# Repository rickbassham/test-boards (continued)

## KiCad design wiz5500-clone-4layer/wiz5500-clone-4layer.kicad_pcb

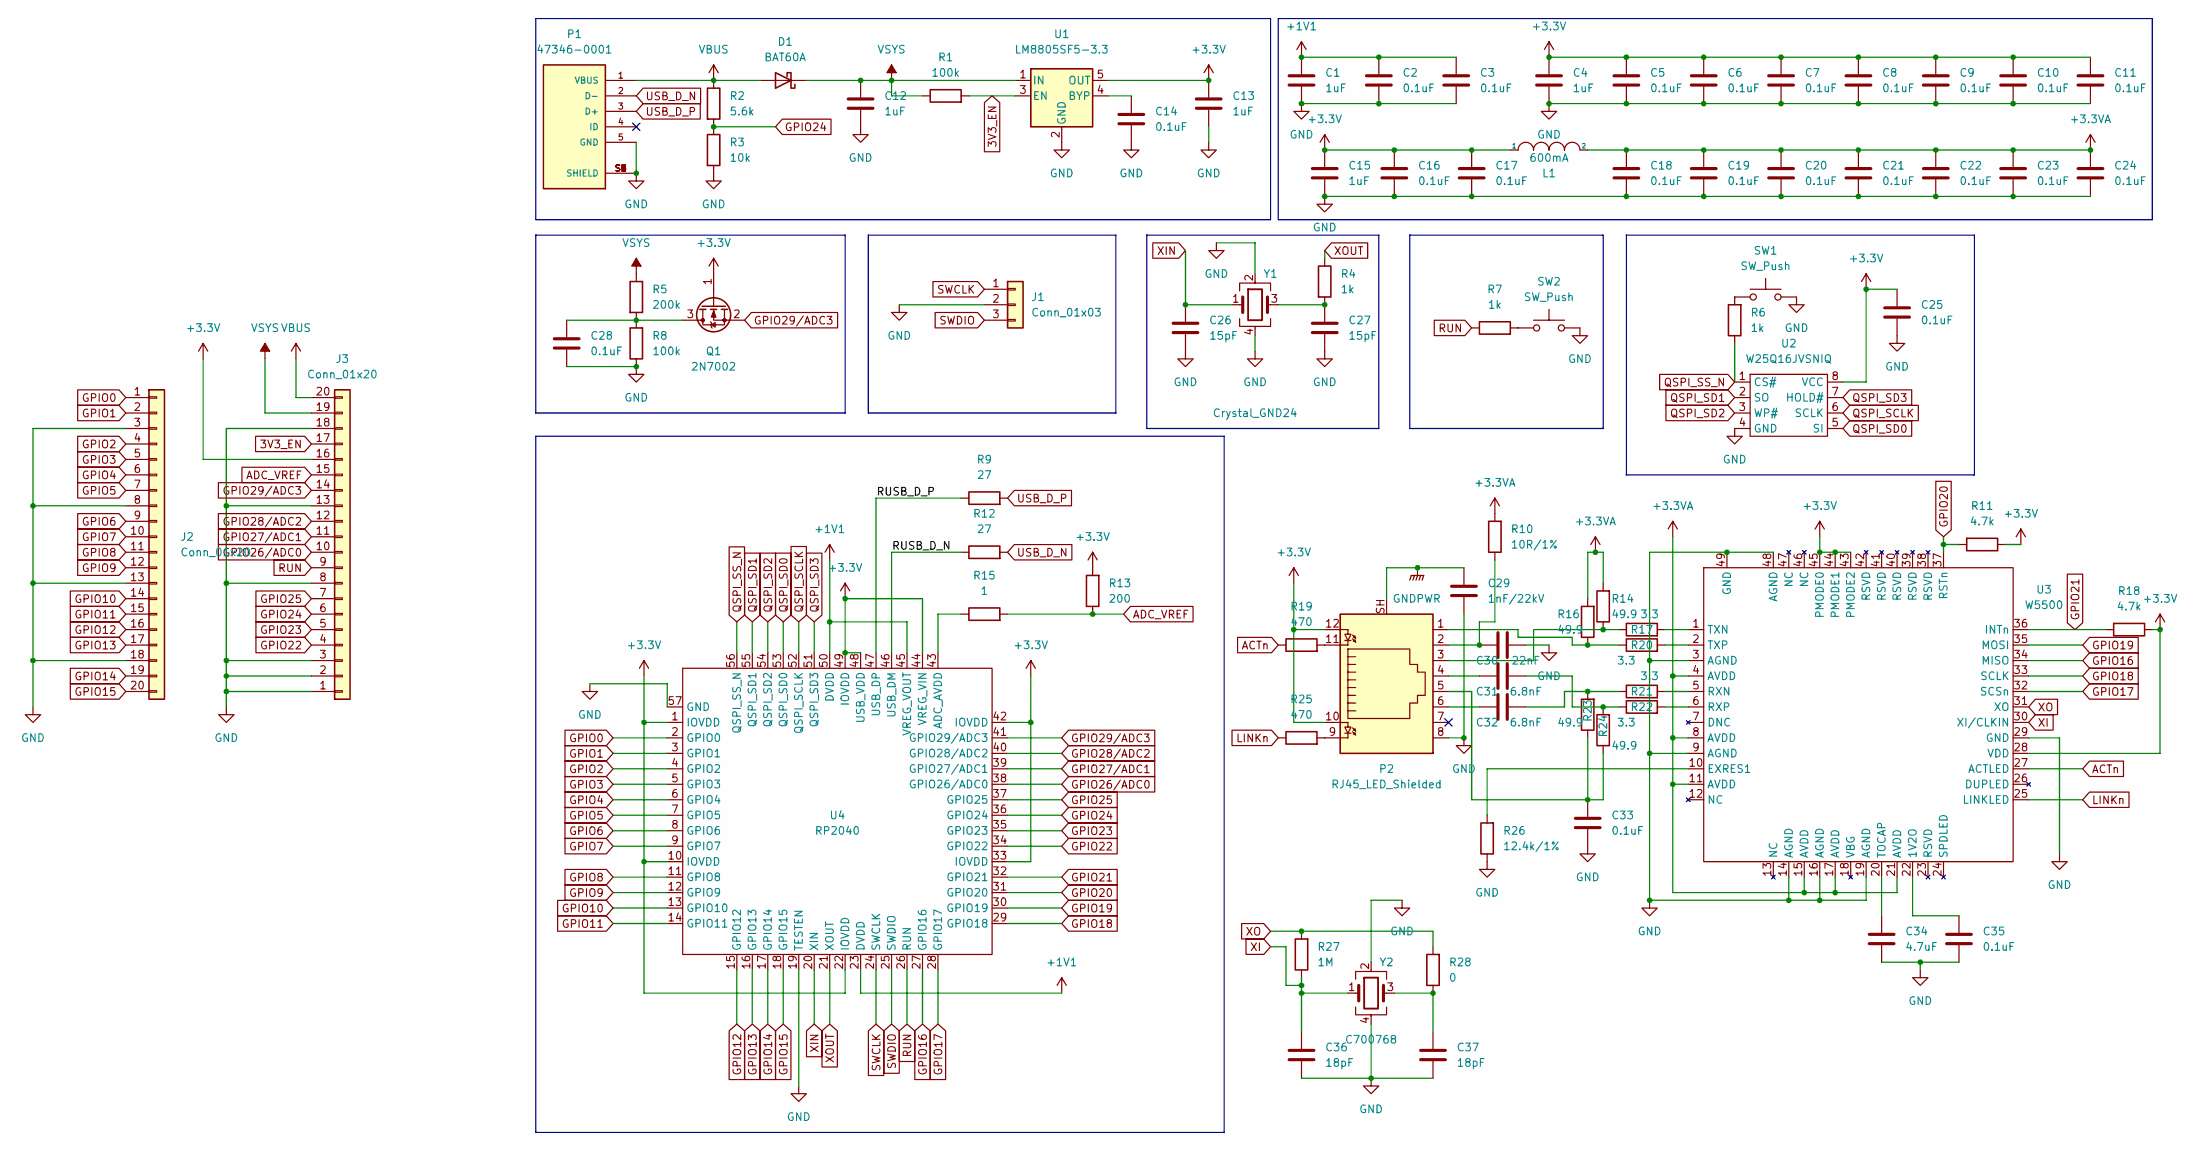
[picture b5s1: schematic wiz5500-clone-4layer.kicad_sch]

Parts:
C1, C4, C12, C13, C15: 1uF; C_0402_1005Metric; LCSC C52923
C2, C3, C5, C6, C7, C8, C9, C10, C11, C14, C16, C17, C18, C19, C20, C21, C22, C23, C24, C25, C28, C33, C35: 0.1uF; C_0402_1005Metric; LCSC C1525
C26, C27: 15pF; C_0402_1005Metric; LCSC C1548
C29: 1nF/22kV; C_1812_4532Metric; LCSC C304032
C30: 22nF; C_0402_1005Metric; LCSC C1532
C31, C32: 6.8nF; C_0402_1005Metric; LCSC C1542
C34: 4.7uF; C_0402_1005Metric; LCSC C23733
C36, C37: 18pF; C_0402_1005Metric; LCSC C1549
D1: BAT60A; D_SOD-323; Manufacturer PN BAT60AE6327HTSA1; LCSC C520634
J1: Conn_01x03; PinHeader_1x03_P2.54mm_Vertical
J2, J3: Conn_01x20; PinHeader_1x20_P2.54mm_Vertical
L1: 600mA; L_0603_1608Metric; LCSC C280478
P1: 47346-0001; MOLEX_47346-0001; LCSC C132560
P2: RJ45_LED_Shielded; J1B1211CCD; Manufacturer PN J1B1211CCD; LCSC C910371
Q1: 2N7002; SOT-23; LCSC C8545
R1, R8: 100k; R_0402_1005Metric; LCSC C25741
R2: 5.6k; R_0402_1005Metric; LCSC C25908
R3: 10k; R_0402_1005Metric; LCSC C25744
R4, R6, R7: 1k; R_0402_1005Metric; LCSC C11702
R5: 200k; R_0402_1005Metric; LCSC C25764
R9, R12: 27; R_0603_1608Metric; LCSC C25190
R10: 10R/1%; R_0402_1005Metric; LCSC C25077
R11, R18: 4.7k; R_0402_1005Metric; LCSC C25900
R13: 200; R_0402_1005Metric; LCSC C25087
R14, R16, R23, R24: 49.9; R_0402_1005Metric; LCSC C25120
R15: 1; R_0402_1005Metric; LCSC C25086
R17, R20, R21, R22: 3.3; R_0402_1005Metric; LCSC C270612
R19, R25: 470; R_0402_1005Metric; LCSC C25117
R26: 12.4k/1%; R_0402_1005Metric; LCSC C11692
R27: 1M; R_0402_1005Metric; LCSC C26083
R28: 0; R_0402_1005Metric; LCSC C17168
SW1, SW2: SW_Push; SW_TS-1187A-B-A-B; LCSC C318884
U1: LM8805SF5-3.3; SOT-23-5; LCSC C126077
U2: W25Q16JVSNIQ; SOIC-8_3.9x4.9mm_P1.27mm; LCSC C115407
U3: W5500; LQFP-48-1EP_7x7mm_P0.5mm_EP3.6x3.6mm; LCSC C32843
U4: RP2040; LCSC C2040
Y1: Crystal_GND24; Crystal_SMD_3225-4Pin_3.2x2.5mm; LCSC C133334
Y2: C700768; Crystal_SMD_3225-4Pin_3.2x2.5mm; LCSC C700768

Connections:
3V3_EN: J3.17, R1.2, U1.3 (EN)
+1V1: C1.1, C2.1, C3.1, U4.23 (DVDD), U4.45 (VREG_VOUT), U4.50 (DVDD)
+3.3VA: C18.1, C19.1, C20.1, C21.1, C22.1, C23.1, C24.1, L1.2, R10.2, R14.2, R16.2, U3.4 (AVDD), U3.8 (AVDD), U3.11 (AVDD), U3.15 (AVDD), U3.17 (AVDD), U3.21 (AVDD)
+3V3: C4.1, C5.1, C6.1, C7.1, C8.1, C9.1, C10.1, C11.1, C13.1, C15.1, C16.1, C17.1, C25.1, J3.16, L1.1, P2.10, P2.12, Q1.1 (G), R11.1, R13.2, R18.1, U1.5 (OUT), U2.8 (VCC), U3.28 (VDD), U3.43 (PMODE2), U3.44 (PMODE1), U3.45 (PMODE0), U4.1 (IOVDD), U4.10 (IOVDD), U4.22 (IOVDD), U4.33 (IOVDD), U4.42 (IOVDD), U4.44 (VREG_VIN), U4.48 (USB_VDD), U4.49 (IOVDD)
/RUSB_D_N: R12.1, U4.46 (USB_DM)
/RUSB_D_P: R9.1, U4.47 (USB_DP)
ACTn: R19.1, U3.27 (ACTLED)
ADC_VREF: J3.15, R13.1, R15.2
GND: C1.2, C2.2, C3.2, C4.2, C5.2, C6.2, C7.2, C8.2, C9.2, C10.2, C11.2, C12.2, C13.2, C14.2, C15.2, C16.2, C17.2, C18.2, C19.2, C20.2, C21.2, C22.2, C23.2, C24.2, C25.2, C26.2, C27.2, C28.2, C29.2, C30.2, C33.2, C34.2, C35.2, C36.2, C37.2, J1.2, J2.3, J2.8, J2.13, J2.18, J3.1, J3.2, J3.3, J3.8, J3.13, J3.18, P1.5 (GND), P1.S1 (SHIELD), P1.S2 (SHIELD), P1.S3 (SHIELD), P1.S4 (SHIELD), P1.S5 (SHIELD), P1.S6 (SHIELD), P2.8, R3.2, R8.1, R26.1, SW1.2, SW2.2, U1.2 (GND), U2.4 (GND), U3.3 (AGND), U3.9 (AGND), U3.14 (AGND), U3.16 (AGND), U3.19 (AGND), U3.29 (GND), U3.48 (AGND), U3.49 (GND), U4.19 (TESTEN), U4.57 (GND), Y1.2, Y1.4, Y2.2, Y2.4
GNDPWR: C29.1, P2.SH
GPIO0: J2.1, U4.2 (GPIO0)
GPIO1: J2.2, U4.3 (GPIO1)
GPIO2: J2.4, U4.4 (GPIO2)
GPIO3: J2.5, U4.5 (GPIO3)
GPIO4: J2.6, U4.6 (GPIO4)
GPIO5: J2.7, U4.7 (GPIO5)
GPIO6: J2.9, U4.8 (GPIO6)
GPIO7: J2.10, U4.9 (GPIO7)
GPIO8: J2.11, U4.11 (GPIO8)
GPIO9: J2.12, U4.12 (GPIO9)
GPIO10: J2.14, U4.13 (GPIO10)
GPIO11: J2.15, U4.14 (GPIO11)
GPIO12: J2.16, U4.15 (GPIO12)
GPIO13: J2.17, U4.16 (GPIO13)
GPIO14: J2.19, U4.17 (GPIO14)
GPIO15: J2.20, U4.18 (GPIO15)
GPIO16: U3.34 (MISO), U4.27 (GPIO16)
GPIO17: U3.32 (SCSn), U4.28 (GPIO17)
GPIO18: U3.33 (SCLK), U4.29 (GPIO18)
GPIO19: U3.35 (MOSI), U4.30 (GPIO19)
GPIO20: R11.2, U3.37 (RSTn), U4.31 (GPIO20)
GPIO21: R18.2, U3.36 (INTn), U4.32 (GPIO21)
GPIO22: J3.4, U4.34 (GPIO22)
GPIO23: J3.5, U4.35 (GPIO23)
GPIO24: J3.6, R2.2, R3.1, U4.36 (GPIO24)
GPIO25: J3.7, U4.37 (GPIO25)
GPIO26/ADC0: J3.10, U4.38 (GPIO26/ADC0)
GPIO27/ADC1: J3.11, U4.39 (GPIO27/ADC1)
GPIO28/ADC2: J3.12, U4.40 (GPIO28/ADC2)
GPIO29/ADC3: J3.14, Q1.2 (S), U4.41 (GPIO29/ADC3)
LINKn: R25.1, U3.25 (LINKLED)
unnamed: C14.1, U1.4 (BYP)
unnamed: C27.1, R4.2, Y1.3
unnamed: C28.1, Q1.3 (D), R5.2, R8.2
unnamed: C30.1, P2.2, R10.1
unnamed: C31.1, P2.4
unnamed: C31.2, R22.1, R24.2
unnamed: C32.1, P2.6
unnamed: C32.2, R21.1, R23.2
unnamed: C33.1, P2.5, R23.1, R24.1
unnamed: C34.1, U3.20 (TOCAP)
unnamed: C35.1, U3.22 (1V2O)
unnamed: C37.1, R28.1, Y2.3
unnamed: P2.1, R16.1, R20.1
unnamed: P2.3, R14.1, R17.1
unnamed: P2.9, R25.2
unnamed: P2.11, R19.2
unnamed: R6.2, SW1.1
unnamed: R7.2, SW2.1
unnamed: R15.1, U4.43 (ADC_AVDD)
unnamed: R17.2, U3.1 (TXN)
unnamed: R20.2, U3.2 (TXP)
unnamed: R21.2, U3.5 (RXN)
unnamed: R22.2, U3.6 (RXP)
unnamed: R26.2, U3.10 (EXRES1)
QSPI_SCLK: U2.6 (SCLK), U4.52 (QSPI_SCLK)
QSPI_SD0: U2.5 (SI), U4.53 (QSPI_SD0)
QSPI_SD1: U2.2 (SO), U4.55 (QSPI_SD1)
QSPI_SD2: U2.3 (WP#), U4.54 (QSPI_SD2)
QSPI_SD3: U2.7 (HOLD#), U4.51 (QSPI_SD3)
QSPI_SS_N: R6.1, U2.1 (CS#), U4.56 (QSPI_SS_N)
RUN: J3.9, R7.1, U4.26 (RUN)
SWCLK: J1.1, U4.24 (SWCLK)
SWDIO: J1.3, U4.25 (SWDIO)
USB_D_N: P1.2 (D-), R12.2
USB_D_P: P1.3 (D+), R9.2
VBUS: D1.2 (A), J3.20, P1.1 (VBUS), R2.1
VSYS: C12.1, D1.1 (K), J3.19, R1.1, R5.1, U1.1 (IN)
XI: C36.1, R27.1, U3.30 (XI/CLKIN), Y2.1
XIN: C26.1, U4.20 (XIN), Y1.1
XO: R27.2, R28.2, U3.31 (XO)
XOUT: R4.1, U4.21 (XOUT)

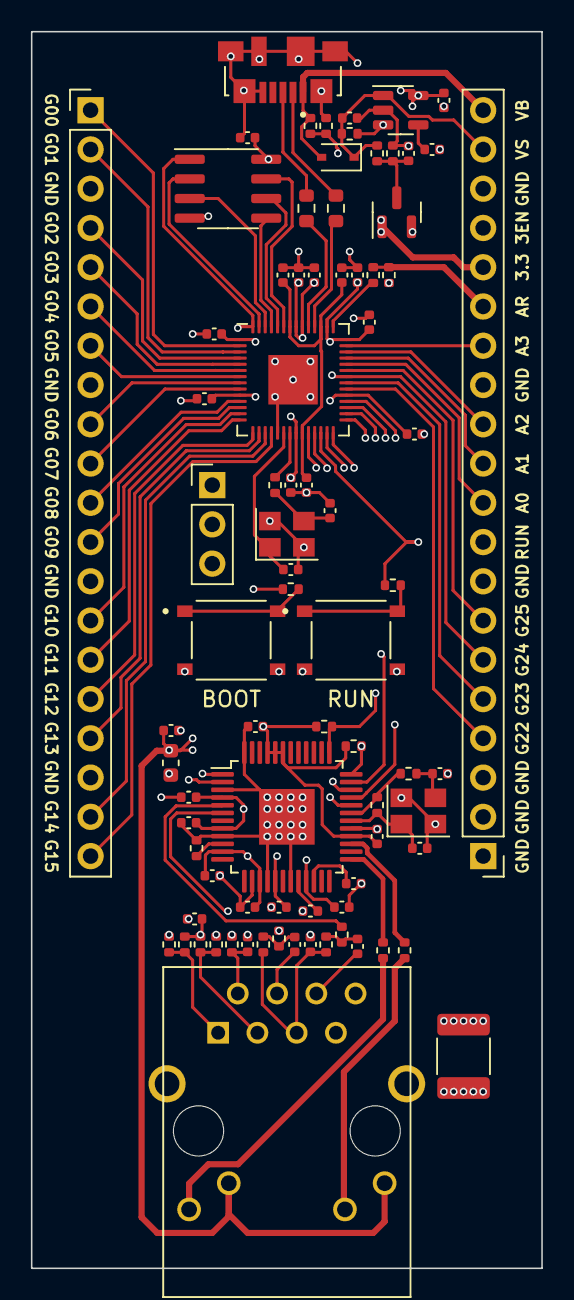
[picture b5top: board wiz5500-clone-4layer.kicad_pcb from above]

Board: 4 copper layers, 33.0 x 80.0 mm, 81 parts (0 on the bottom side), 82 nets.

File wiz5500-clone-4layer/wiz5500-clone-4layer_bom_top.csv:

"Comment","Designator","Footprint","LCSC Part #"
"1uF","C1 C4 C12 C13 C15","","C52923"
"0.1uF","C2 C3 C5 C6 C7 C8 C9 C10 C11 C14 C16 C17 C18 C19 C20 C21 C22 C23 C24 C25 C28 C33 C35","","C1525"
"15pF","C26 C27","","C1548"
"1nF/22kV","C29","","C304032"
"22nF","C30","","C1532"
"6.8nF","C31 C32","","C1542"
"4.7uF","C34","","C23733"
"18pF","C36 C37","","C1549"
"BAT60A","D1","","C520634"
"Conn_01x03","J1","",""
"Conn_01x20","J2 J3","",""
"600mA","L1","","C280478"
"47346-0001","P1","","C132560"
"RJ45_LED_Shielded","P2","","C910371"
"2N7002","Q1","","C8545"
"100k","R1 R8","","C25741"
"5.6k","R2","","C25908"
"10k","R3","","C25744"
"1k","R4 R6 R7","","C11702"
"200k","R5","","C25764"
"27","R9 R12","","C25190"
"10R/1%","R10","","C25077"
"4.7k","R11 R18","","C25900"
"200","R13","","C25087"
"49.9","R14 R16 R23 R24","","C25120"
"1","R15","","C25086"
"3.3","R17 R20 R21 R22","","C270612"
"470","R19 R25","","C25117"
"12.4k/1%","R26","","C11692"
"1M","R27","","C26083"
"0","R28","","C17168"
"SW_Push","SW1 SW2","","C318884"
"LM8805SF5-3.3","U1","","C126077"
"GD25Q16ETIGR","U2","","C520634"
"W5500","U3","","C32843"
"RP2040","U4","","C2040"
"Crystal_GND24","Y1","","C133334"
"C700768","Y2","","C700768"
